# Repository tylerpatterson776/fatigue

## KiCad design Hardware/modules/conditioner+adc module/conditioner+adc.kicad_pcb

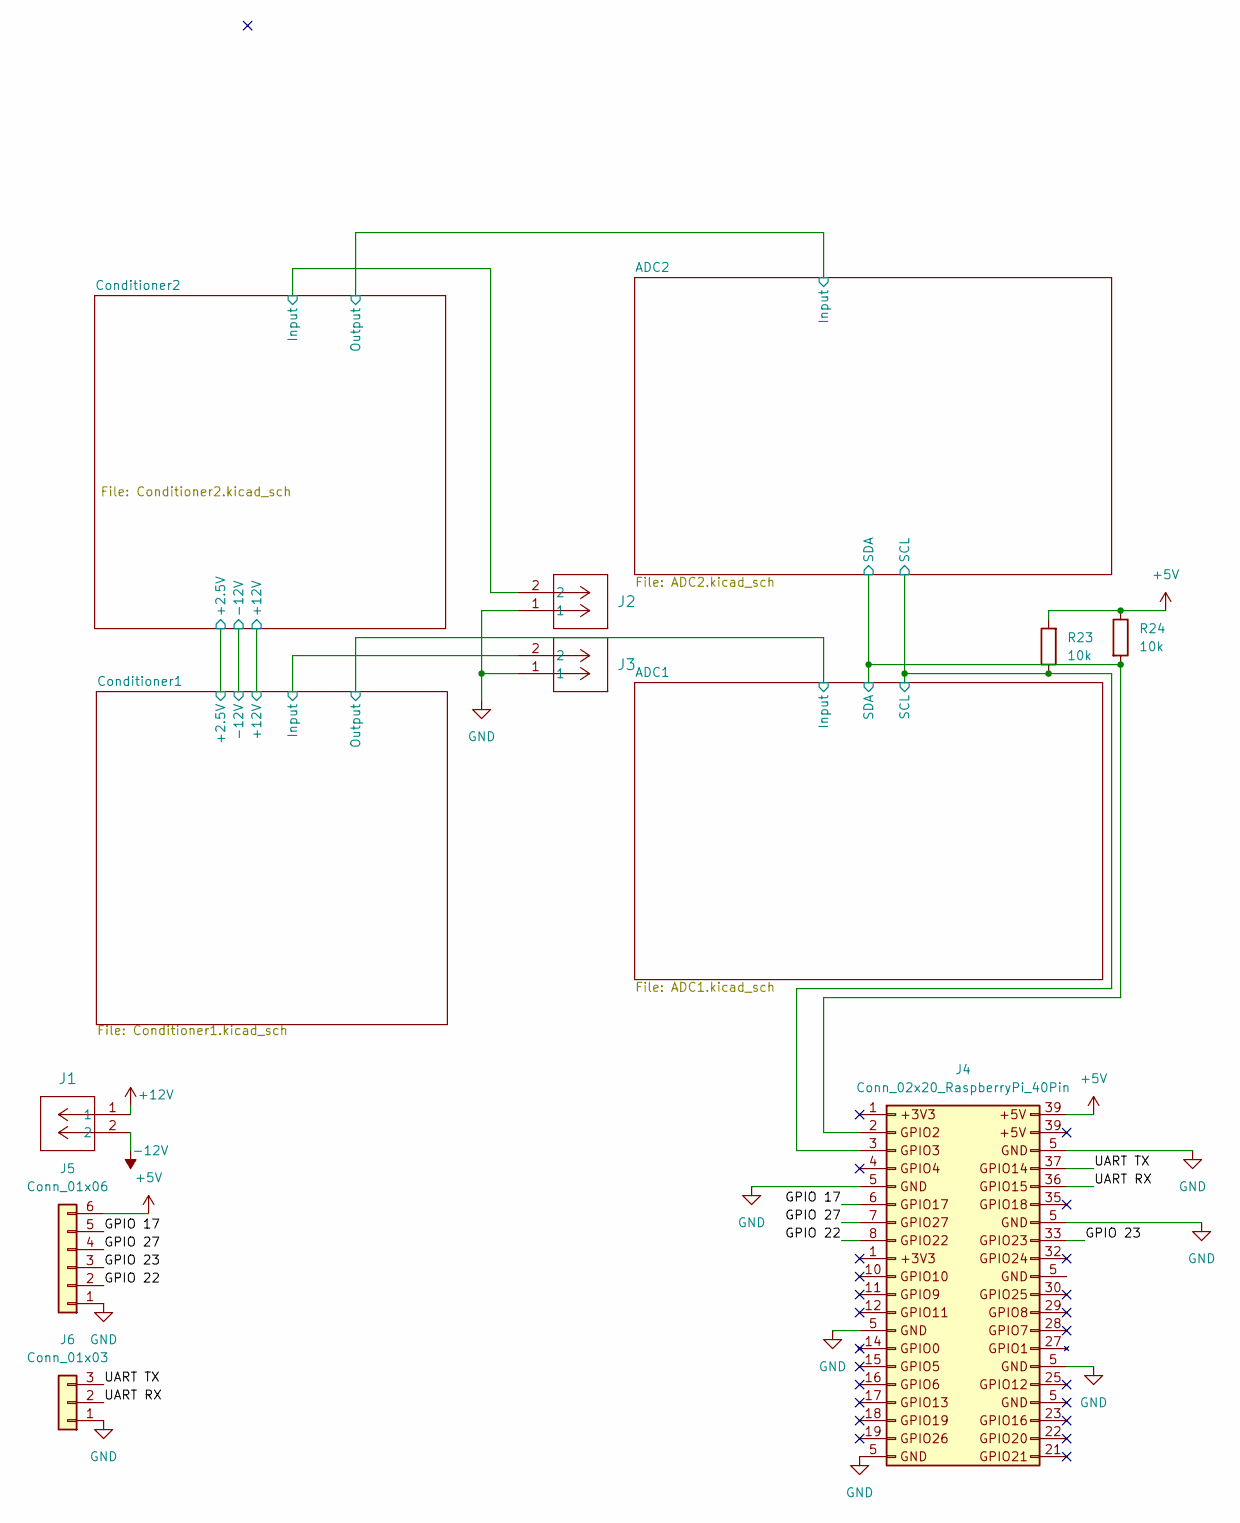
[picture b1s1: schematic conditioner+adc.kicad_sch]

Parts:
J1, J2, J3: CONN_JST_1x2_1.25mmPitch
J4: Conn_02x20_RaspberryPi_40Pin; CONN_RASPBERRYPI_40PIN_2x20
J5: Conn_01x06; CONN_JST_1x6_1.25mmPitch
J6: Conn_01x03; CONN_JST_1x3_1.25mmPitch
R23, R24: 10k; R_0805_2012Metric_Pad1.20x1.40mm_HandSolder

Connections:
+5V: J4.39, J5.6, R23.2, R24.1; also elsewhere on the board
+12V: J1.1; also elsewhere on the board
-12V: J1.2; also elsewhere on the board
/ADC1/SCL: J4.3, R23.1; also elsewhere on the board
/ADC1/SDA: J4.2, R24.2; also elsewhere on the board
/Conditioner1/Input: J3.2; also elsewhere on the board
/Conditioner2/Input: J2.2; also elsewhere on the board
/GPIO 17: J4.6, J5.5
/GPIO 22: J4.8, J5.2
/GPIO 23: J4.33, J5.3
/GPIO 27: J4.7, J5.4
/UART RX: J4.36, J6.2
/UART TX: J4.37, J6.3
GND: J2.1, J3.1, J4.5, J5.1, J6.1; also elsewhere on the board

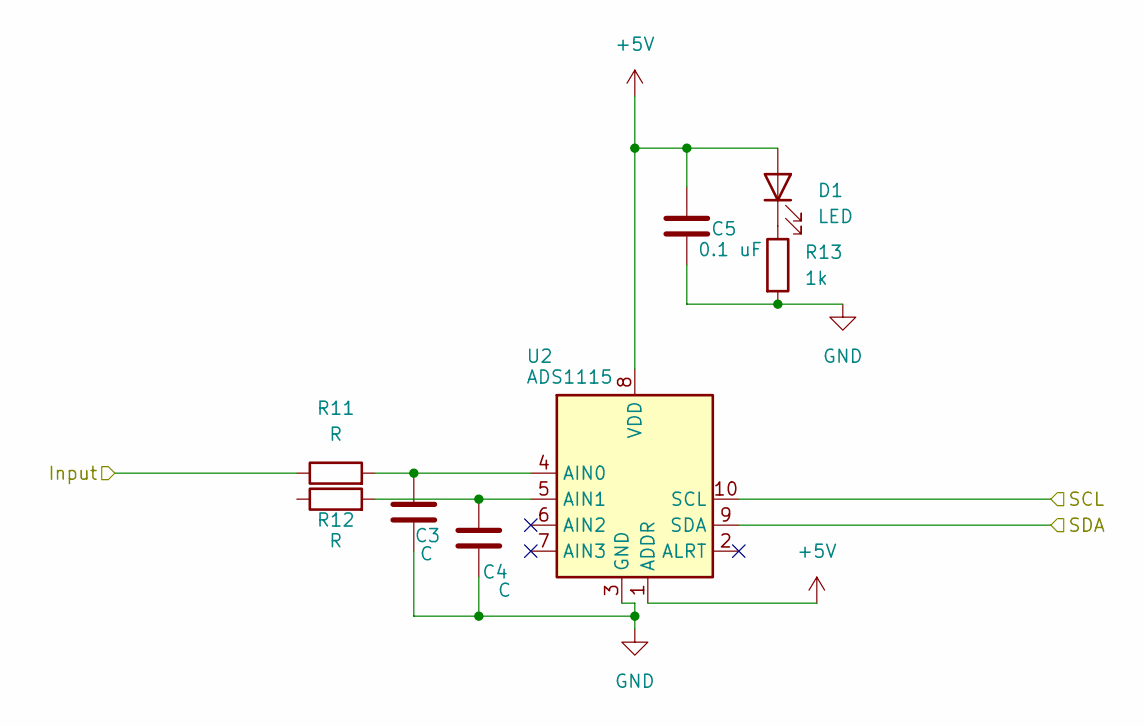
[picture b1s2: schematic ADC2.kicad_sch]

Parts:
C3, C4: C; C_0805_2012Metric_Pad1.18x1.45mm_HandSolder
C5: 0.1 uF; C_0805_2012Metric_Pad1.18x1.45mm_HandSolder
D1: LED; LED_0805_2012Metric_Pad1.15x1.40mm_HandSolder
R11, R12: R; R_0805_2012Metric_Pad1.20x1.40mm_HandSolder
R13: 1k; R_0805_2012Metric_Pad1.20x1.40mm_HandSolder
U2: ADS1115; TSSOP-10_3x3mm_P0.5mm

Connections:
+5V: C5.2, D1.2 (A), U2.1 (ADDR), U2.8 (VDD); also elsewhere on the board
/ADC1/SCL: U2.10 (SCL); also elsewhere on the board
/ADC1/SDA: U2.9 (SDA); also elsewhere on the board
/ADC2/Input: R11.1; also elsewhere on the board
GND: C3.2, C4.2, C5.1, R13.2, U2.3 (GND); also elsewhere on the board
unnamed: D1.1 (K), R13.1
unnamed: C3.1, R11.2, U2.4 (AIN0)
unnamed: C4.1, R12.2, U2.5 (AIN1)

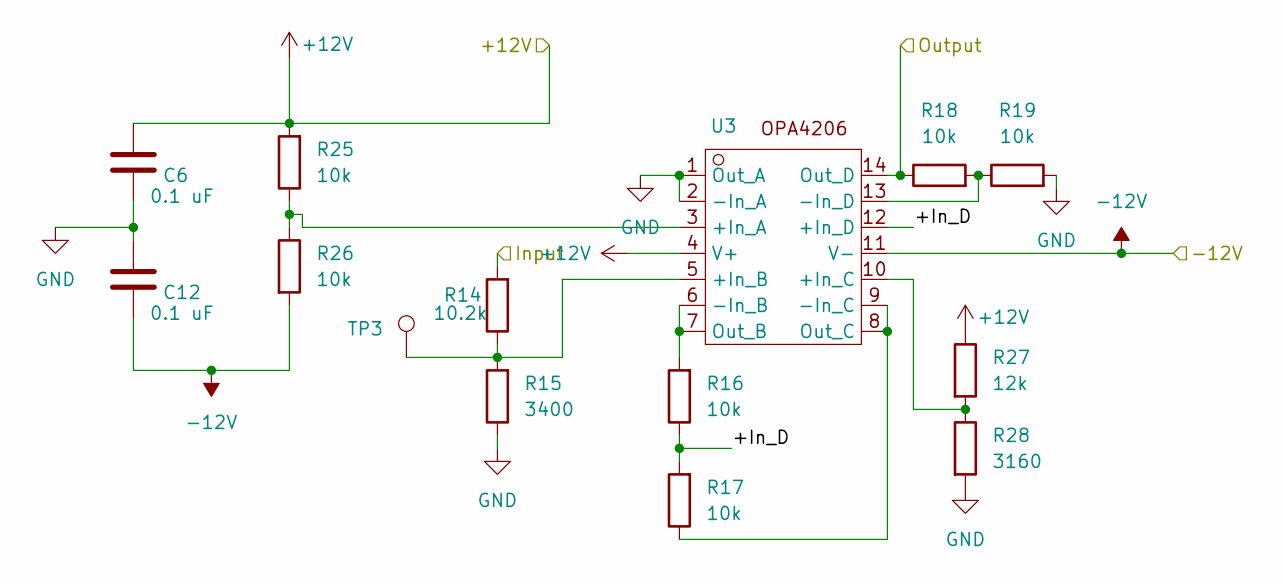
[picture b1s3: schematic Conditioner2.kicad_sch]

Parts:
C6, C12: 0.1 uF; C_0805_2012Metric_Pad1.18x1.45mm_HandSolder
R14: 10.2k; R_1206_3216Metric_Pad1.30x1.75mm_HandSolder
R15: 3400; R_1206_3216Metric_Pad1.30x1.75mm_HandSolder
R16, R17, R18, R19: 10k; R_0805_2012Metric_Pad1.20x1.40mm_HandSolder
R25, R26: 10k; R_1206_3216Metric_Pad1.30x1.75mm_HandSolder
R27: 12k; R_1206_3216Metric_Pad1.30x1.75mm_HandSolder
R28: 3160; R_1206_3216Metric_Pad1.30x1.75mm_HandSolder
TP3: TestPoint; TestPoint_Pad_D2.0mm
U3: SOIC-14_3.9x8.7mm_P1.27mm

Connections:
+12V: C6.1, R25.2, R27.1, U3.4 (V+); also elsewhere on the board
-12V: C12.2, R26.2, U3.11 (V-); also elsewhere on the board
/ADC2/Input: R18.1, U3.14 (Out_D); also elsewhere on the board
/Conditioner2/+In_D: R16.1, R17.2, U3.12 (+In_D)
/Conditioner2/Input: R14.2; also elsewhere on the board
GND: C6.2, C12.1, R15.1, R19.2, R28.2, U3.1 (Out_A), U3.2 (-In_A); also elsewhere on the board
unnamed: R25.1, R26.1, U3.3 (+In_A)
unnamed: R14.1, R15.2, TP3.1, U3.5 (+In_B)
unnamed: R27.2, R28.1, U3.10 (+In_C)
unnamed: R16.2, U3.6 (-In_B), U3.7 (Out_B)
unnamed: R17.1, U3.8 (Out_C), U3.9 (-In_C)
unnamed: R18.2, R19.1, U3.13 (-In_D)

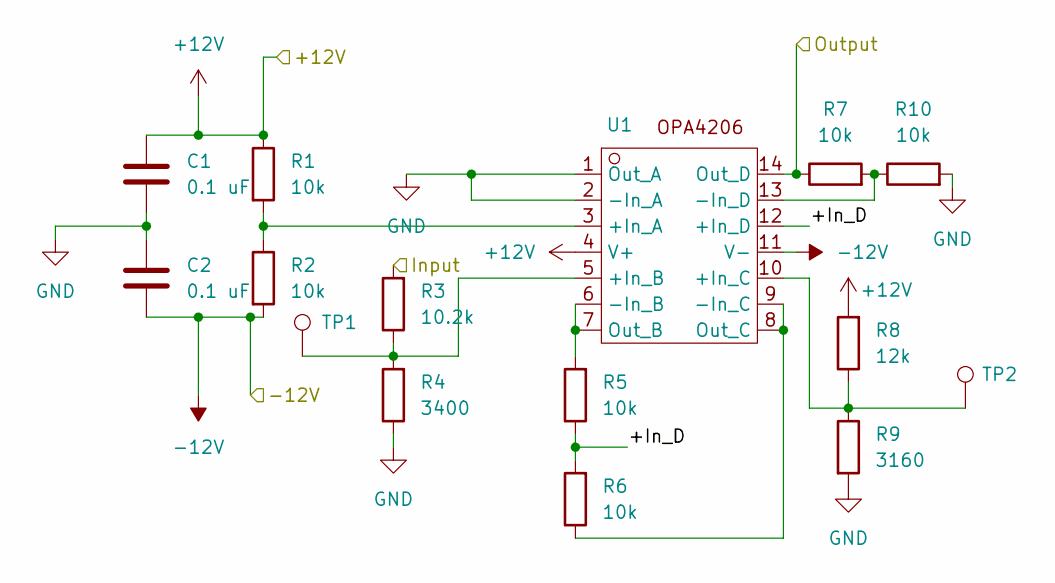
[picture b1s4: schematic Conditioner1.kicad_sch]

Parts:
C1, C2: 0.1 uF; C_0805_2012Metric_Pad1.18x1.45mm_HandSolder
R1, R2, R5, R6, R7, R10: 10k; R_0805_2012Metric_Pad1.20x1.40mm_HandSolder
R3: 10.2k; R_1206_3216Metric_Pad1.30x1.75mm_HandSolder
R4: 3400; R_1206_3216Metric_Pad1.30x1.75mm_HandSolder
R8: 12k; R_1206_3216Metric_Pad1.30x1.75mm_HandSolder
R9: 3160; R_1206_3216Metric_Pad1.30x1.75mm_HandSolder
TP1, TP2: TestPoint; TestPoint_Pad_D2.0mm
U1: SOIC-14_3.9x8.7mm_P1.27mm

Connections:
+12V: C1.1, R1.1, R8.2, U1.4 (V+); also elsewhere on the board
-12V: C2.2, R2.2, U1.11 (V-); also elsewhere on the board
/ADC1/Input: R7.1, U1.14 (Out_D); also elsewhere on the board
/Conditioner1/+In_D: R5.1, R6.2, U1.12 (+In_D)
/Conditioner1/Input: R3.2; also elsewhere on the board
GND: C1.2, C2.1, R4.1, R9.2, R10.2, U1.1 (Out_A), U1.2 (-In_A); also elsewhere on the board
unnamed: R1.2, R2.1, U1.3 (+In_A)
unnamed: R3.1, R4.2, TP1.1, U1.5 (+In_B)
unnamed: R8.1, R9.1, TP2.1, U1.10 (+In_C)
unnamed: R5.2, U1.6 (-In_B), U1.7 (Out_B)
unnamed: R6.1, U1.8 (Out_C), U1.9 (-In_C)
unnamed: R7.2, R10.1, U1.13 (-In_D)

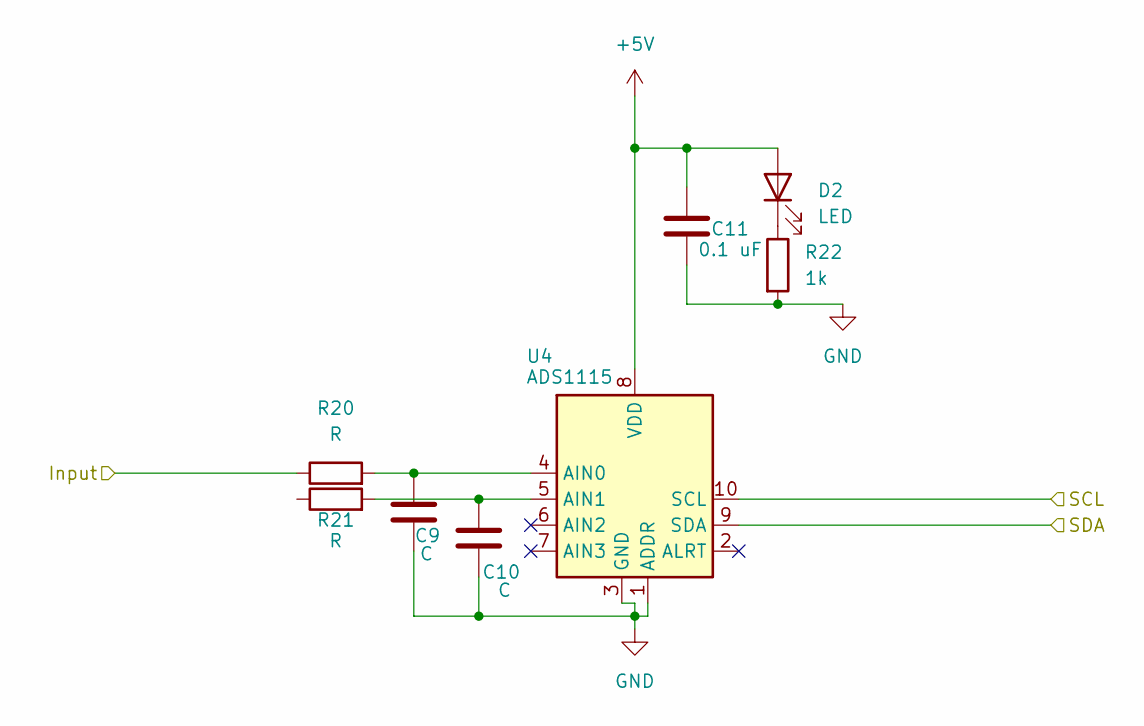
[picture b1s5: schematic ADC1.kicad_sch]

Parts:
C9, C10: C; C_0805_2012Metric_Pad1.18x1.45mm_HandSolder
C11: 0.1 uF; C_0805_2012Metric_Pad1.18x1.45mm_HandSolder
D2: LED; LED_0805_2012Metric_Pad1.15x1.40mm_HandSolder
R20, R21: R; R_0805_2012Metric_Pad1.20x1.40mm_HandSolder
R22: 1k; R_0805_2012Metric_Pad1.20x1.40mm_HandSolder
U4: ADS1115; TSSOP-10_3x3mm_P0.5mm

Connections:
+5V: C11.2, D2.2 (A), U4.8 (VDD); also elsewhere on the board
/ADC1/Input: R20.1; also elsewhere on the board
/ADC1/SCL: U4.10 (SCL); also elsewhere on the board
/ADC1/SDA: U4.9 (SDA); also elsewhere on the board
GND: C9.2, C10.2, C11.1, R22.2, U4.1 (ADDR), U4.3 (GND); also elsewhere on the board
unnamed: D2.1 (K), R22.1
unnamed: C9.1, R20.2, U4.4 (AIN0)
unnamed: C10.1, R21.2, U4.5 (AIN1)

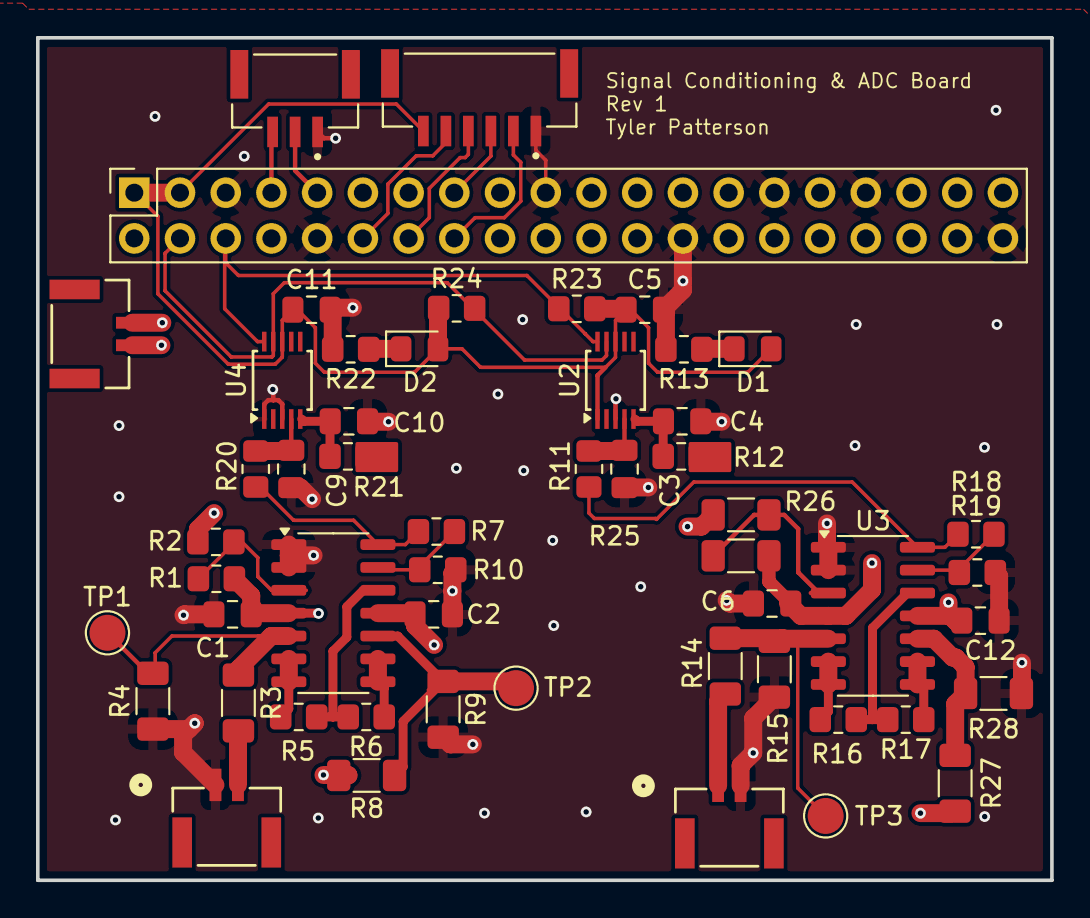
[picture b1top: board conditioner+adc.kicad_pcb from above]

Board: 4 copper layers, 56.3 x 46.8 mm, 53 parts (0 on the bottom side), 36 nets.

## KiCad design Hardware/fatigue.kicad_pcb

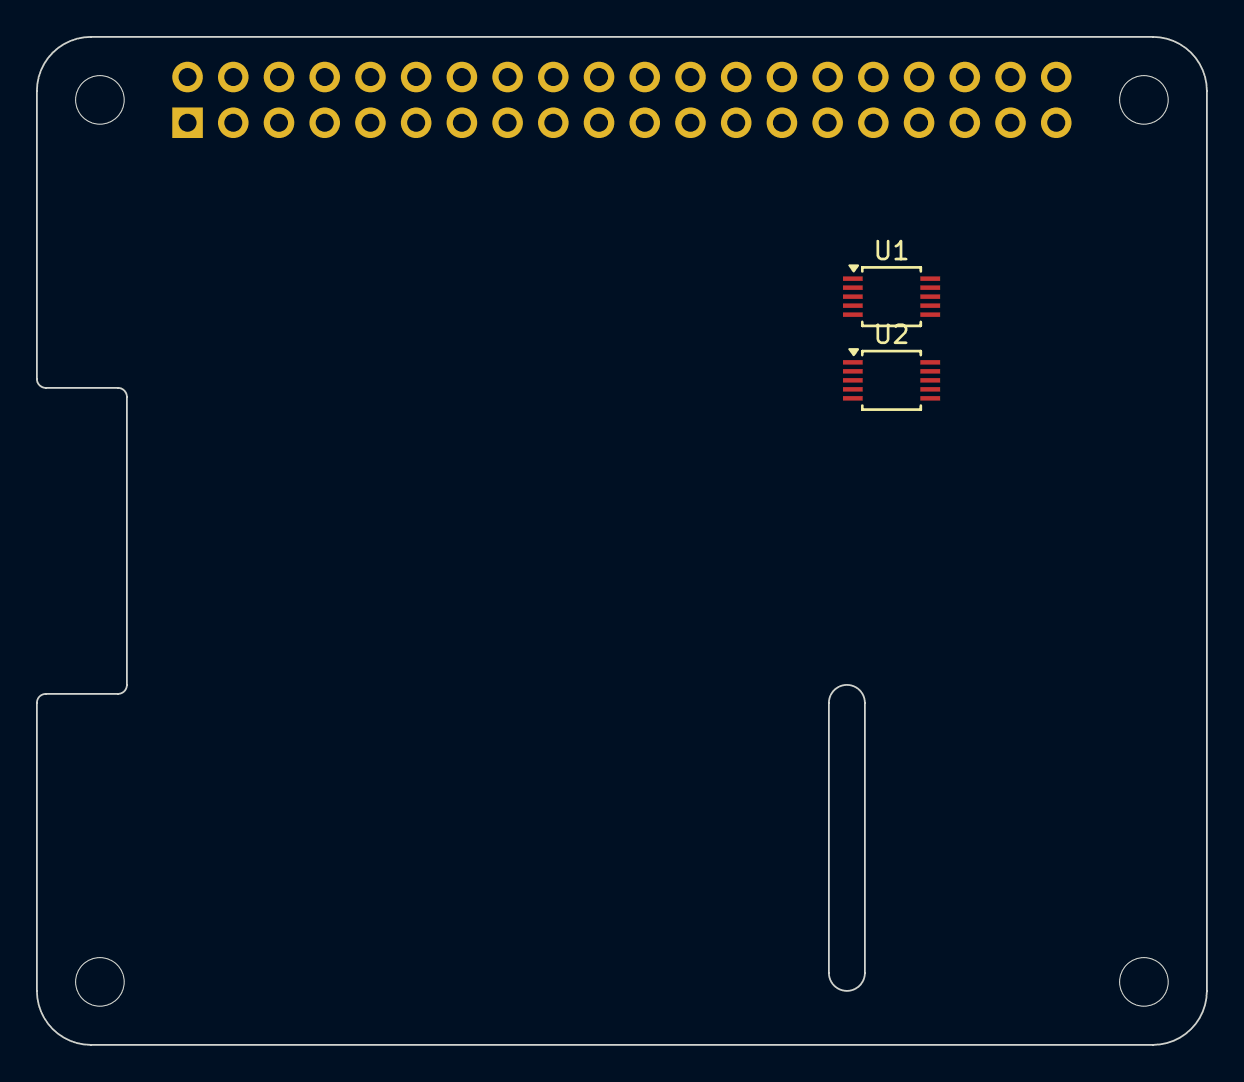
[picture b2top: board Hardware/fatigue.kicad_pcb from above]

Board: 2 copper layers, 65.0 x 56.0 mm, 7 parts (1 on the bottom side), 6 nets, no tracks yet.

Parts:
J1: GPIO; PinSocket_2x20_P2.54mm_Vertical
MH1, MH2, MH3, MH4: MountingHole_2.7mm_M2.5
U1, U2: ADS1115IDGS; TSSOP-10_3x3mm_P0.5mm

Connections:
+3V3: J1.1, J1.17
+5V: U1.1 (ADDR), U1.8 (VDD), U2.8 (VDD)
GND: J1.6, J1.9, J1.14, J1.20, J1.25, J1.30, J1.34, J1.39, U1.3 (GND), U1.5 (AIN1), U1.6 (AIN2), U1.7 (AIN3), U2.1 (ADDR), U2.3 (GND), U2.5 (AIN1), U2.6 (AIN2), U2.7 (AIN3)
unnamed: U1.10 (SCL), U2.10 (SCL)
unnamed: U1.9 (SDA), U2.9 (SDA)
PI +5V: J1.2, J1.4

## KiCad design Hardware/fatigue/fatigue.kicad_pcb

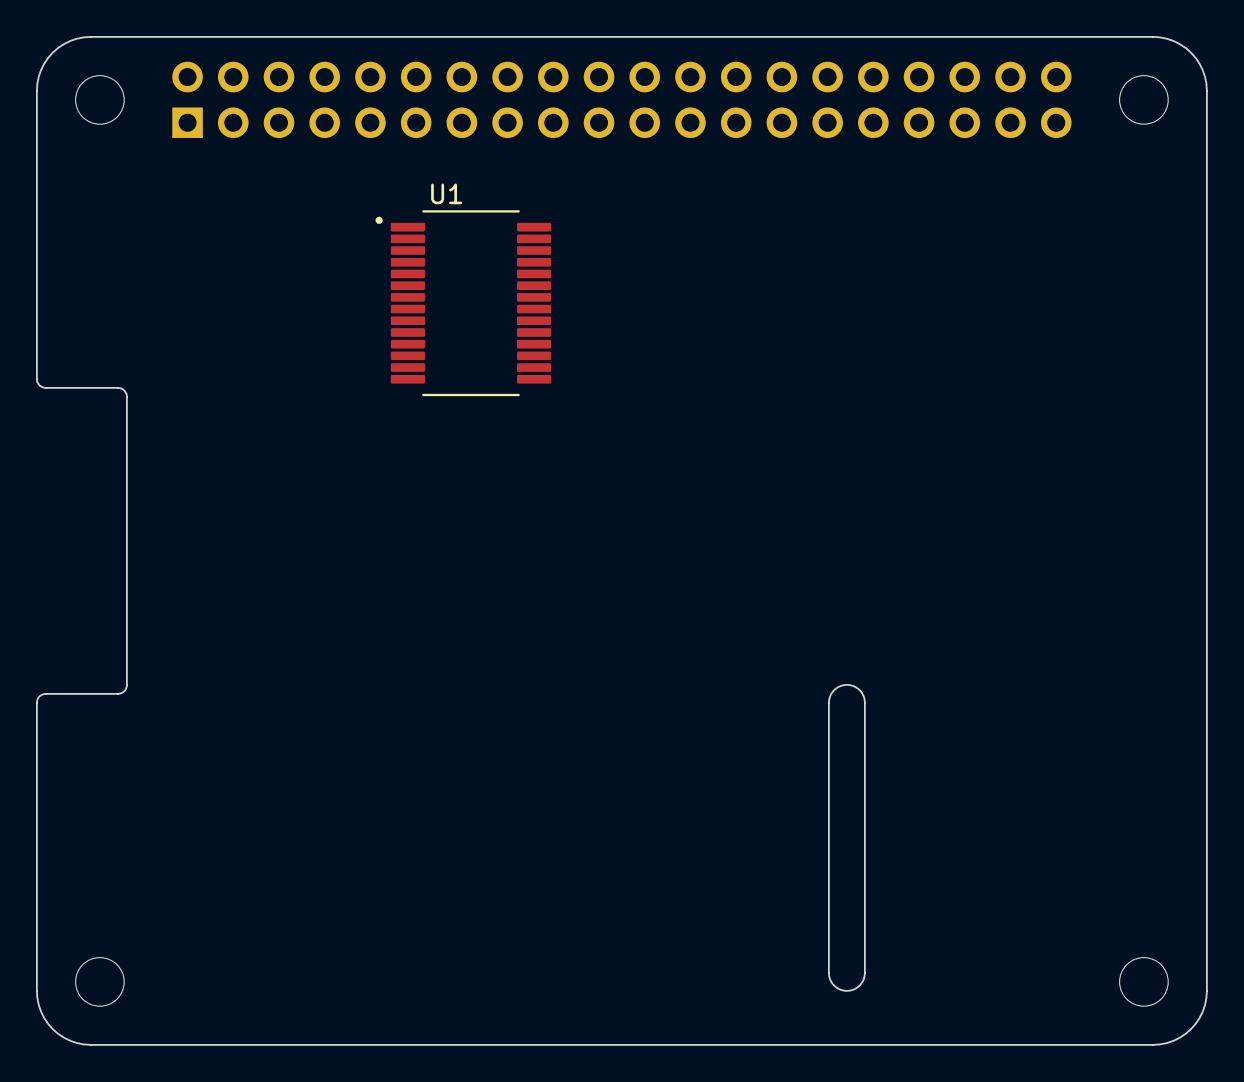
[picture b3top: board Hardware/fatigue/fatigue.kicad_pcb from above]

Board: 2 copper layers, 65.0 x 56.0 mm, 6 parts (1 on the bottom side), 7 nets, no tracks yet.

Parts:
J1: GPIO; PinSocket_2x20_P2.54mm_Vertical
MH1, MH2, MH3, MH4: MountingHole_2.7mm_M2.5
U1: ADS1256IDBR; IC_ADC_ADS1256IDBR

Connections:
+3V3: J1.1, J1.17, U1.16 (DVDD)
+5V: J1.2, J1.4, U1.1 (AVDD)
/GPIO8/SPI0.CE0: J1.24, U1.20 (~CS)
/GPIO9/SPI0.MISO: J1.21, U1.22 (DOUT)
/GPIO10/SPI0.MOSI: J1.19, U1.23 (DIN)
/GPIO11/SPI0.SCLK: J1.23, U1.24 (SCLK)
GND: J1.6, J1.9, J1.14, J1.20, J1.25, J1.30, J1.34, J1.39, U1.2 (AGND), U1.17 (DGND)

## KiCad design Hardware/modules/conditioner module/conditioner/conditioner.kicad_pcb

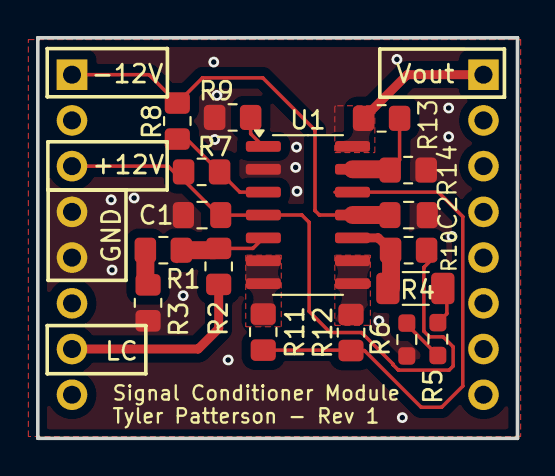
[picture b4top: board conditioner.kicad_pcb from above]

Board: 2 copper layers, 26.7 x 22.2 mm, 19 parts (0 on the bottom side), 16 nets.

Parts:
C1, C2: 0.1 uF; C_0805_2012Metric_Pad1.18x1.45mm_HandSolder
J1, J2: Conn_01x08_MountingPin; PinHeader_1x08_P2.54mm_Vertical
R1: 3.3k; R_0805_2012Metric_Pad1.20x1.40mm_HandSolder
R2, R7, R8, R10, R11, R12, R13, R14: 10k; R_0805_2012Metric_Pad1.20x1.40mm_HandSolder
R3: 33.2; R_0805_2012Metric_Pad1.20x1.40mm_HandSolder
R4: 2.5K; R_1206_3216Metric_Pad1.30x1.75mm_HandSolder
R5: 130; R_0603_1608Metric_Pad0.98x0.95mm_HandSolder
R6: 1.58; R_0603_1608Metric_Pad0.98x0.95mm_HandSolder
R9: 1k; R_0805_2012Metric_Pad1.20x1.40mm_HandSolder
U1: SOIC-14_3.9x8.7mm_P1.27mm

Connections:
+12V: C1.1, J1.3, R7.1, R10.2, U1.4 (V+)
-12V: C2.2, J1.1, R8.2, U1.11 (V-)
/+In_D: R11.1, R12.2, U1.12 (+In_D)
/LC_S: J1.7, R2.2
/output: J2.1, R13.1, U1.14 (Out_D)
GND: C1.2, C2.1, J1.4, J1.5, R3.2, R6.2, R9.1, R14.2, U1.2 (-In_A)
unnamed: R1.2, R3.1
unnamed: R4.2, R5.1
unnamed: R5.2, R6.1
unnamed: R7.2, R8.1, U1.3 (+In_A)
unnamed: R1.1, R2.1, U1.5 (+In_B)
unnamed: R4.1, R10.1, U1.10 (+In_C)
unnamed: R11.2, U1.6 (-In_B), U1.7 (Out_B)
unnamed: R12.1, U1.8 (Out_C), U1.9 (-In_C)
unnamed: R13.2, R14.1, U1.13 (-In_D)
unnamed: R9.2, U1.1 (Out_A)

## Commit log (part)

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2025-07-30 Create motor
    trying to mak this not terrible
2025-07-30 Rename motor to motor.c
2025-10-26 setting this up
2025-10-26 aaaaa
2025-10-26 ok this should be fine
2025-10-27 The fatigue machine pcb is born
2025-10-27 The fatigue machine PCB is really born
2025-11-02 bruh
2025-11-03 the big update
2025-11-03 more changes
2025-11-18 aaaa
2026-01-17 The big one
2026-02-02 syncing this all up
2026-02-04 signal conditioner module stuffs
2026-04-07 Initial commit for fatigue-machine UI.
2026-04-09 Implemented data logging.
2026-04-09 Added saving to logs/ directory.
2026-04-14 Implemented frequency estimation for load and distance charts. Added hover support to view chart datapoints.
